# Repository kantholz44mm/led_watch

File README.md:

# Description

It's a wristwatch using LEDs to show the current time. This repository contains one major folder for the hardware part, which contains a KiCAD project with the schematics & PCB layout, as well as a FreeCAD project with 3D-printable parts for the case. You can find instructions on how to use each "part" of the repo in the subfolders.

# How it works

The watch has a (very) low power STM32 microcontroller, as well as a Bosch BMA400 accelerometer for user inputs. It also has a 32 kHz crystal for precise timekeeping. A ring of 60 LEDs shows the hour and minute hands when the watch is doubletapped on its X axis. When not displaying the time, all components are put into their lowest possible power modes, consuming ~9uA total. Since the device is powered by a single CR2032 or CR2016 coin cell on the back of the PCB, this results in a theoretical maximum runtime of up to ~2.9. I have not had time to test this fully, but my personal watch has been going strong on a single cell for around 7 months with daily use. Battery lifetime of course heavily depends on how often the display is activated.

# Design Goals

- Long battery life & Easy battery replacement
- Small diameter (currently 38mm without the case)
- Manufacturability (case is 3D-printable or machineable)
- Water-tightness

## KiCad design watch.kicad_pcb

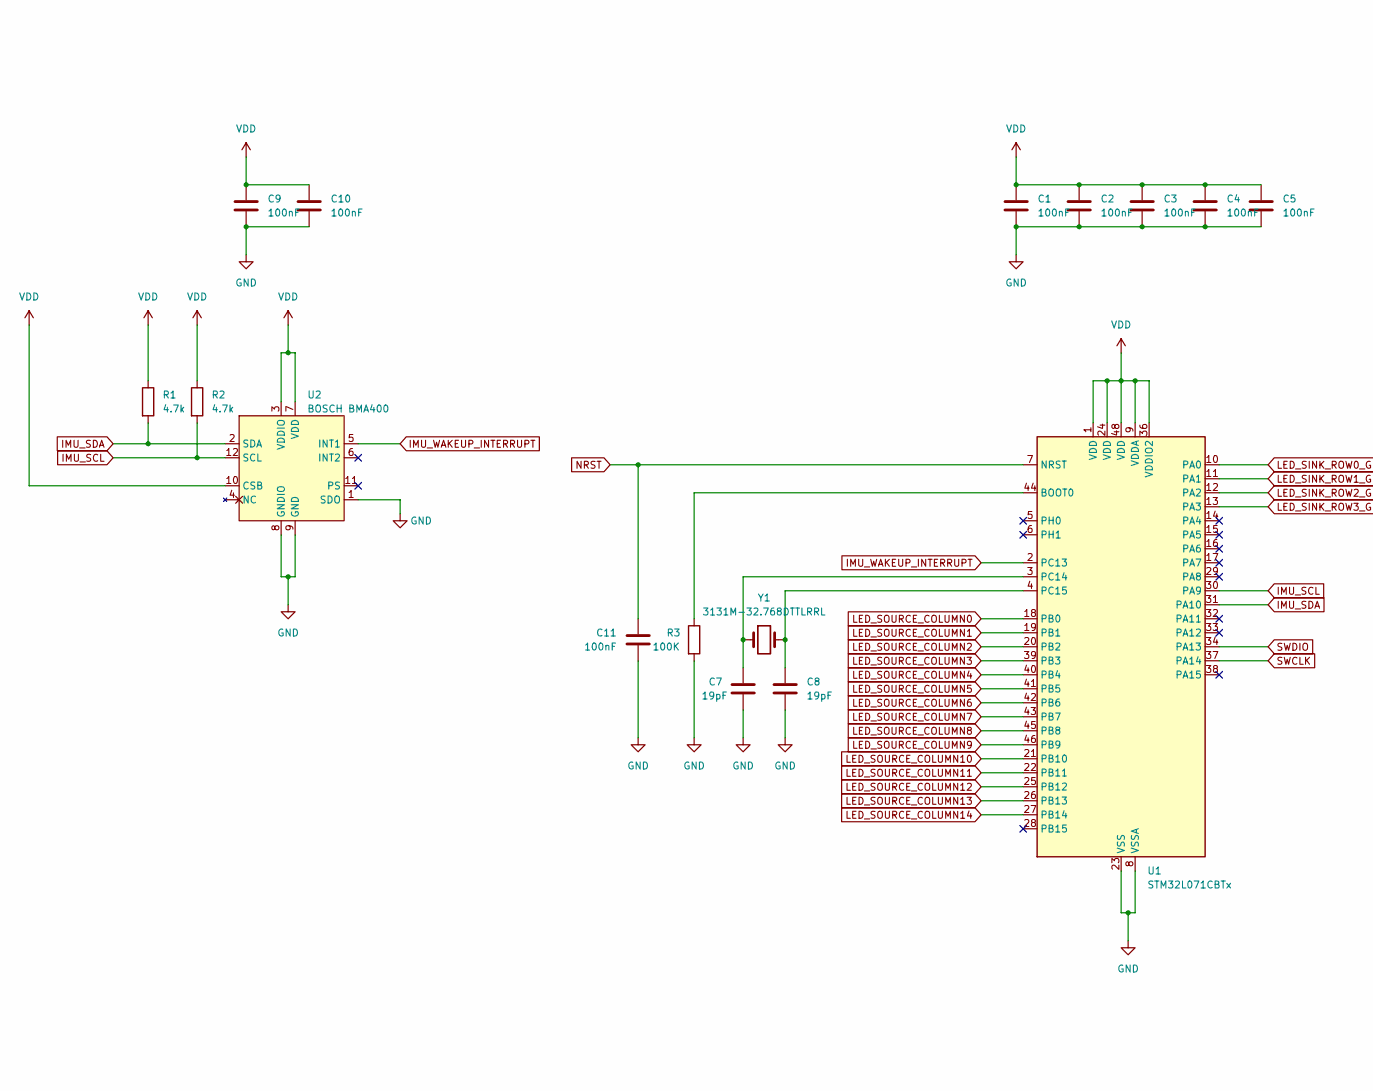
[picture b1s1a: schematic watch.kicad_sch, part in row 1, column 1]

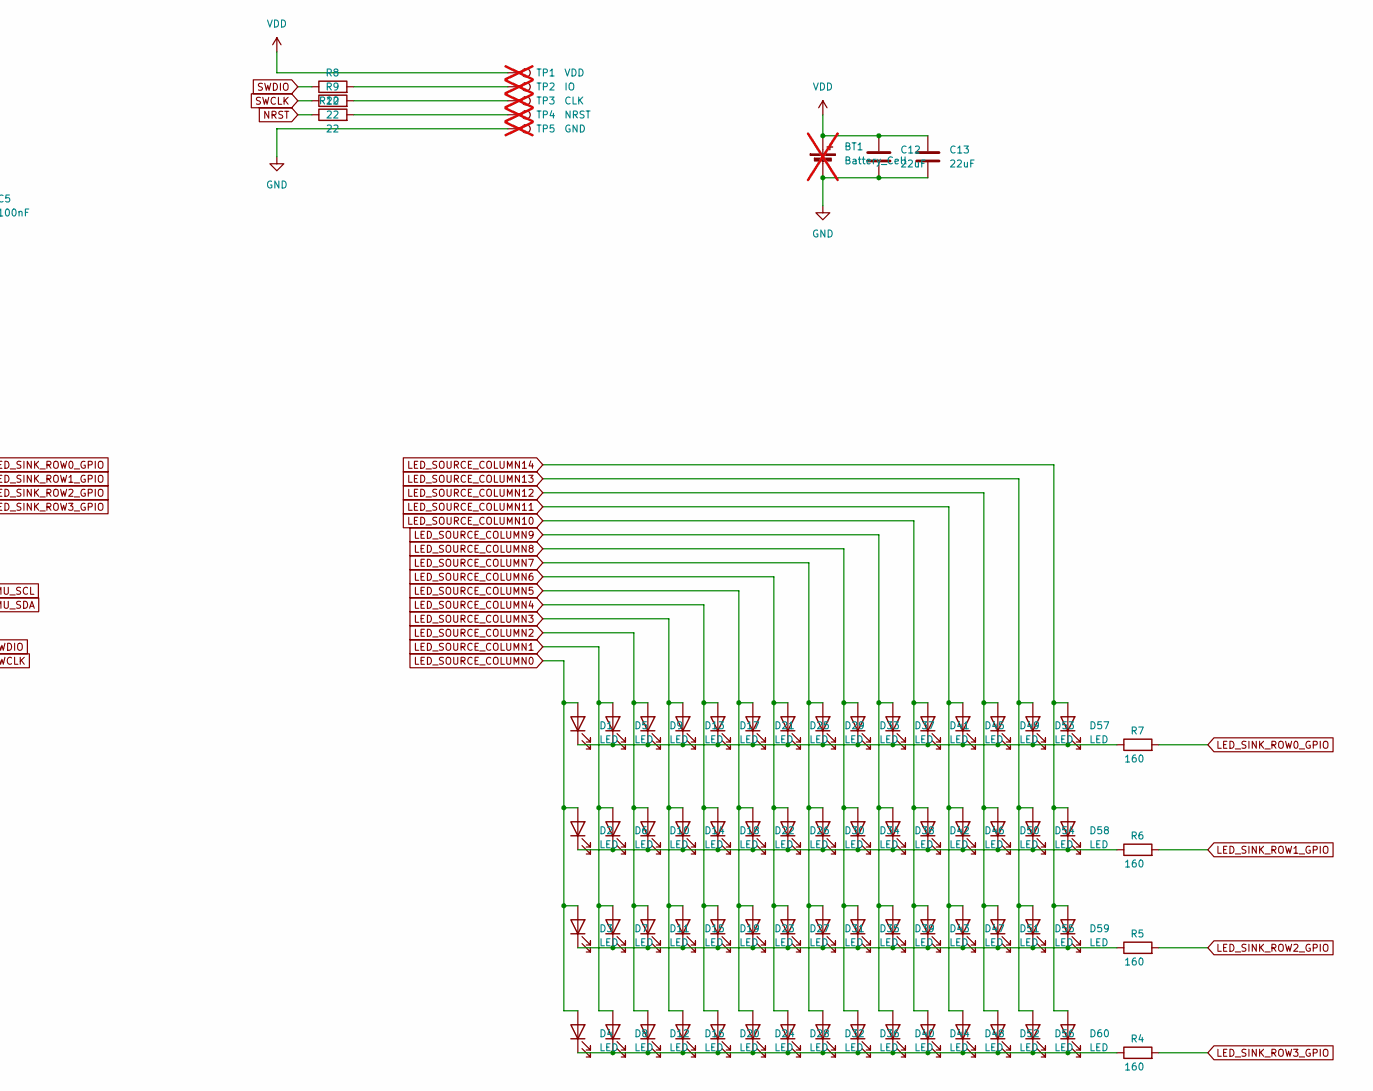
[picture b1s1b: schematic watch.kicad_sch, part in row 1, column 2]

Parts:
BT1: Battery_Cell; BatteryHolder_MPD_BC2003_1x2032; not fitted
C1, C2, C3, C4, C5, C9, C10, C11: 100nF; C_0603_1608Metric; LCSC Part # C91183
C7, C8: 19pF; C_0603_1608Metric; LCSC Part # C527046
C12, C13: 22uF; C_0603_1608Metric; LCSC Part # C86295
D1, D2, D3, D4, D5, D6, D7, D8, D9, D10, D11, D12, D13, D14, D15, D16, D17, D18, D19, D20, D21, D22, D23, D24, D25, D26, D27, D28, D29, D30, D31, D32, D33, D34, D35, D36, D37, D38, D39, D40, D41, D42, D43, D44, D45, D46, D47, D48, D49, D50, D51, D52, D53, D54, D55, D56, D57, D58, D59, D60: LED; 0603; LCSC Part # C284922
R1, R2: 4.7k; R_0603_1608Metric; LCSC Part # C23162
R3: 100K; R_0603_1608Metric; LCSC Part # C25805
R4, R5, R6, R7: 160; R_0603_1608Metric; LCSC Part # C22814
R8, R9, R10: 22; R_0603_1608Metric; LCSC Part # C23345
TP1: VDD; TestPoint_Pad_D2.0mm; not fitted
TP2: IO; TestPoint_Pad_D2.0mm; not fitted
TP3: CLK; TestPoint_Pad_D2.0mm; not fitted
TP4: NRST; TestPoint_Pad_D2.0mm; not fitted
TP5: GND; TestPoint_Pad_D2.0mm; not fitted
U1: STM32L071CBTx; LQFP-48_7x7mm_P0.5mm; LCSC Part # C79758
U2: BOSCH BMA400; LGA-12_2x2mm_P0.5mm; LCSC Part # C437655
Y1: 3131M-32.768DTTLRRL; Crystal_SMD_3215-2Pin_3.2x1.5mm; LCSC Part # C42438016

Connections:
GND: BT1.2 (-), C1.1, C2.1, C3.1, C4.1, C5.1, C7.2, C8.2, C9.1, C10.1, C11.1, C12.1, C13.1, R3.2, TP5.1, U1.8 (VSSA), U1.23 (VSS), U1.35 (VSS), U1.47 (VSS), U2.1 (SDO), U2.8 (GNDIO), U2.9 (GND)
IMU_SCL: R2.2, U1.30 (PA9), U2.12 (SCL)
IMU_SDA: R1.2, U1.31 (PA10), U2.2 (SDA)
IMU_WAKEUP_INTERRUPT: U1.2 (PC13), U2.5 (INT1)
LED_SINK_ROW0_GPIO: R7.2, U1.10 (PA0)
LED_SINK_ROW1_GPIO: R6.2, U1.11 (PA1)
LED_SINK_ROW2_GPIO: R5.2, U1.12 (PA2)
LED_SINK_ROW3_GPIO: R4.2, U1.13 (PA3)
LED_SOURCE_COLUMN0: D1.2 (A), D2.2 (A), D3.2 (A), D4.2 (A), U1.18 (PB0)
LED_SOURCE_COLUMN1: D5.2 (A), D6.2 (A), D7.2 (A), D8.2 (A), U1.19 (PB1)
LED_SOURCE_COLUMN2: D9.2 (A), D10.2 (A), D11.2 (A), D12.2 (A), U1.20 (PB2)
LED_SOURCE_COLUMN3: D13.2 (A), D14.2 (A), D15.2 (A), D16.2 (A), U1.39 (PB3)
LED_SOURCE_COLUMN4: D17.2 (A), D18.2 (A), D19.2 (A), D20.2 (A), U1.40 (PB4)
LED_SOURCE_COLUMN5: D21.2 (A), D22.2 (A), D23.2 (A), D24.2 (A), U1.41 (PB5)
LED_SOURCE_COLUMN6: D25.2 (A), D26.2 (A), D27.2 (A), D28.2 (A), U1.42 (PB6)
LED_SOURCE_COLUMN7: D29.2 (A), D30.2 (A), D31.2 (A), D32.2 (A), U1.43 (PB7)
LED_SOURCE_COLUMN8: D33.2 (A), D34.2 (A), D35.2 (A), D36.2 (A), U1.45 (PB8)
LED_SOURCE_COLUMN9: D37.2 (A), D38.2 (A), D39.2 (A), D40.2 (A), U1.46 (PB9)
LED_SOURCE_COLUMN10: D41.2 (A), D42.2 (A), D43.2 (A), D44.2 (A), U1.21 (PB10)
LED_SOURCE_COLUMN11: D45.2 (A), D46.2 (A), D47.2 (A), D48.2 (A), U1.22 (PB11)
LED_SOURCE_COLUMN12: D49.2 (A), D50.2 (A), D51.2 (A), D52.2 (A), U1.25 (PB12)
LED_SOURCE_COLUMN13: D53.2 (A), D54.2 (A), D55.2 (A), D56.2 (A), U1.26 (PB13)
LED_SOURCE_COLUMN14: D57.2 (A), D58.2 (A), D59.2 (A), D60.2 (A), U1.27 (PB14)
NRST: C11.2, R10.1, U1.7 (NRST)
unnamed: D1.1 (K), D5.1 (K), D9.1 (K), D13.1 (K), D17.1 (K), D21.1 (K), D25.1 (K), D29.1 (K), D33.1 (K), D37.1 (K), D41.1 (K), D45.1 (K), D49.1 (K), D53.1 (K), D57.1 (K), R7.1
unnamed: D2.1 (K), D6.1 (K), D10.1 (K), D14.1 (K), D18.1 (K), D22.1 (K), D26.1 (K), D30.1 (K), D34.1 (K), D38.1 (K), D42.1 (K), D46.1 (K), D50.1 (K), D54.1 (K), D58.1 (K), R6.1
unnamed: D3.1 (K), D7.1 (K), D11.1 (K), D15.1 (K), D19.1 (K), D23.1 (K), D27.1 (K), D31.1 (K), D35.1 (K), D39.1 (K), D43.1 (K), D47.1 (K), D51.1 (K), D55.1 (K), D59.1 (K), R5.1
unnamed: D4.1 (K), D8.1 (K), D12.1 (K), D16.1 (K), D20.1 (K), D24.1 (K), D28.1 (K), D32.1 (K), D36.1 (K), D40.1 (K), D44.1 (K), D48.1 (K), D52.1 (K), D56.1 (K), D60.1 (K), R4.1
unnamed: R8.2, TP2.1
unnamed: R9.2, TP3.1
unnamed: R10.2, TP4.1
unnamed: R3.1, U1.44 (BOOT0)
unnamed: C7.1, U1.3 (PC14), Y1.1
unnamed: C8.1, U1.4 (PC15), Y1.2
SWCLK: R9.1, U1.37 (PA14)
SWDIO: R8.1, U1.34 (PA13)
VDD: BT1.1 (+), C1.2, C2.2, C3.2, C4.2, C5.2, C9.2, C10.2, C12.2, C13.2, R1.1, R2.1, TP1.1, U1.1 (VDD), U1.9 (VDDA), U1.24 (VDD), U1.36 (VDDIO2), U1.48 (VDD), U2.3 (VDDIO), U2.7 (VDD), U2.10 (CSB)

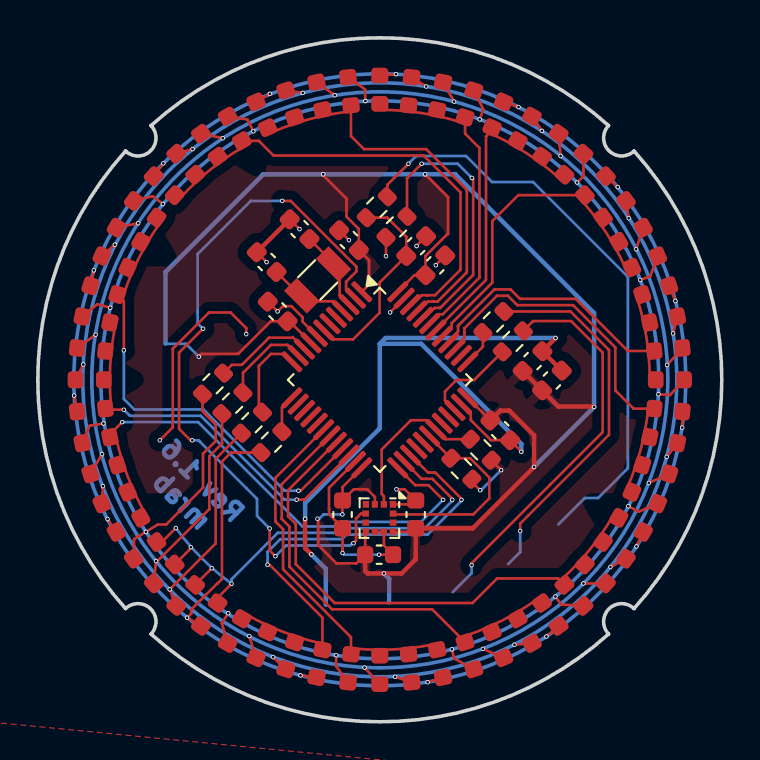
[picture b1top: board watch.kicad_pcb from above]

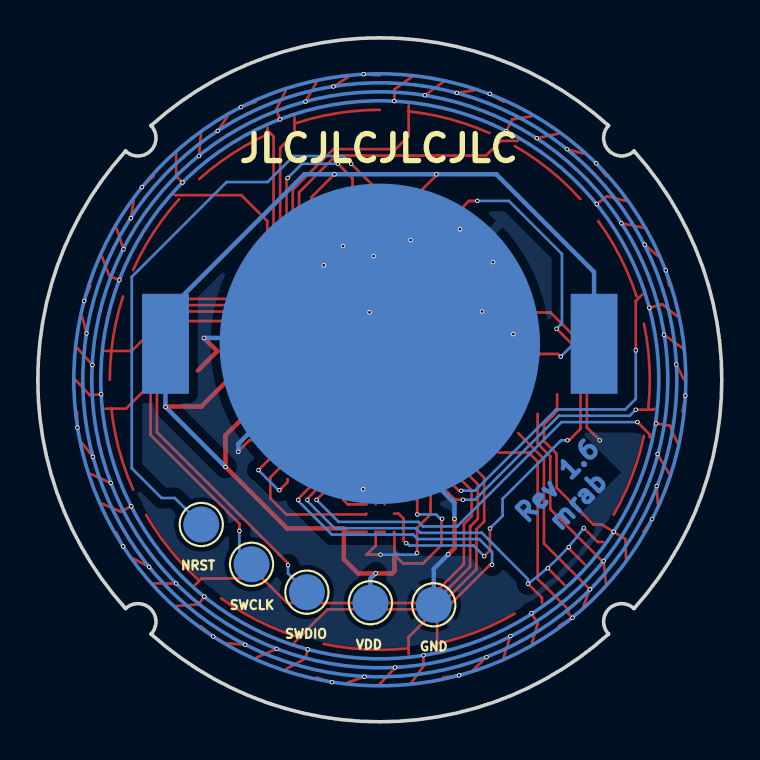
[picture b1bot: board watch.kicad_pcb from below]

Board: 2 copper layers, 38.0 x 38.0 mm, 91 parts (6 on the bottom side), 37 nets.

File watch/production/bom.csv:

Designator,Footprint,Quantity,Value,LCSC Part #
"C1, C10, C11, C2, C3, C4, C5, C9",0603,8,100nF,C91183
"C12, C13",0603,2,22uF,C86295
"C7, C8",0603,2,19pF,C326779
"D1, D10, D11, D12, D13, D14, D15, D16, D17, D18, D19, D2, D20, D21, D22, D23, D24, D25, D26, D27, D28, D29, D3, D30, D31, D32, D33, D34, D35, D36, D37, D38, D39, D4, D40, D41, D42, D43, D44, D45, D46, D47, D48, D49, D5, D50, D51, D52, D53, D54, D55, D56, D57, D58, D59, D6, D60, D7, D8, D9",0603,60,LED,C284922
"R1, R2",0603,2,4.7k,C23162
"R10, R8, R9",0603,3,22,C23345
R3,0603,1,100K,C25805
"R4, R5, R6, R7",0603,4,160,C22814
U1,LQFP-48_7x7mm_P0.5mm,1,STM32L071CBTx,C79758
U2,LGA-12_2x2mm_P0.5mm,1,BOSCH BMA400,C437655
Y1,Crystal_SMD_3215-2Pin_3.2x1.5mm,1,3131M-32.768DTTLRRL,C42438016

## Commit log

2021-11-21 Initial Draft
2021-11-21 no more vias below metallic components; cleaned up some tracks
2021-11-22 V2 after Feedback
2021-11-24 testing gogs
2022-03-23 60 LED version
2022-04-07 as ordered
2022-05-26 as ordered V1.4
2024-06-23 no idea, it's been a while, just saving.
2024-06-23 V2 initial schematic
2024-06-24 V2 PCB first draft
2024-06-24 cleaned up silkscreen
2024-06-25 review
2024-06-26 PCB V2
2024-07-24 small fixes
2024-07-30 good to go
2024-08-01 ready for ordering?
2025-05-21 clean slate.
2025-05-21 V3 first schematic draft done
2025-05-21 added unfinished footprint for DFN0606 FETs
2025-05-22 added DFN0606 footprint
2025-07-14 removed low side FETs, started PCB
2025-07-16 V1.6 basic layout done
2025-07-17 V1.6 done?
2025-07-17 moved stuff around, added .gitignore
2025-08-07 removed old project files
2025-08-07 moved hardware into its own folder
2025-08-07 added software skeleton
2025-08-08 added datasheet
2025-08-12 bma400 working, tap detection and all
2025-08-13 showing time works, animation system done
2025-08-17 i glaub es tut?
2025-10-28 various fixes for software, removed second hand
2025-10-31 case V2 started
2025-11-17 added new case design
2025-11-17 unibody
2026-04-07 fixed geometry of unibody (visual)
2026-04-07 added README
2026-04-08 moved around stuff and added sort of proper READMEs
2026-04-08 Updated README of software, removed proprietary datasheets
2026-04-08 fixed transparent background of state diagram
2026-04-08 added Body & Unibody into single FreeCAD project, added export STLs for Cases
2026-04-08 added export files for binary, Gerbers for PCB
2026-04-08 added hardware README
2026-04-16 Added Apache 2.0 License
